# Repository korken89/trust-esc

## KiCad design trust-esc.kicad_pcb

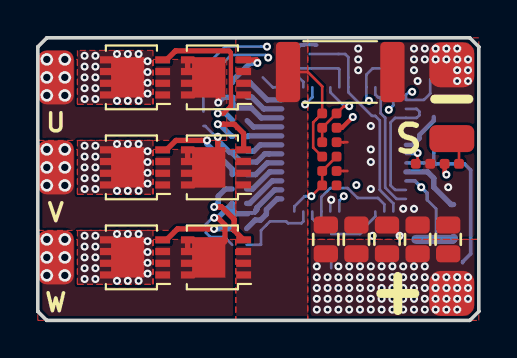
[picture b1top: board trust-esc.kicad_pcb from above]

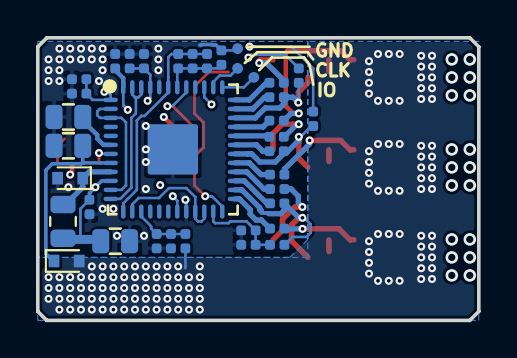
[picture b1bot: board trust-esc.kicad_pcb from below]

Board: 4 copper layers, 24.5 x 15.7 mm, 63 parts (37 on the bottom side), 41 nets.

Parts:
C101, C103, C106, C107, C108, C119: 0.1u; C_0402_1005Metric_Rounded
C102: 47u; C_0805
C104, C105, C111, C112, C113, C114, C116: 6.8u; C_0805
C117: 1n; C_0402_1005Metric_Rounded
C118: 100n; C_0402_1005Metric_Rounded
C501: 22p; C_0402_1005Metric_Rounded
C701, C801, C802: 47p; C_0402_1005Metric_Rounded
D101, D102: NSR05T30XV2T5G; D_SOD-523
J101, J102: Conn_01x01_Male; pad_2.5x2.5mm
J103: Conn_01x01_Male; pad_1.5x2.5mm
J104, J105, J106: Conn_01x01_Male; pad_circ_0.6mm
J201, J301, J401: Conn_01x01_Male; pad_3.0x2.0mm
L101: 22u; L_0805_2012Metric
Q201, Q202, Q301, Q302, Q401, Q402: BUK7M10-40EX; LFPAK33
R102: 100; R_0402_1005Metric_Rounded
R103: 1m; R_2512_6332Metric
R108, R110, R503, R504, R505, R506, R701, R801, R803: 47k; R_0402_1005Metric_Rounded
R109: 2.94k; R_0402_1005Metric_Rounded
R111, R702, R802, R804: 10k; R_0402_1005Metric_Rounded
R201, R202, R301, R302, R401, R402: 10; R_0402_1005Metric_Rounded
R501, R502: 1k; R_0402_1005Metric_Rounded
U101: STSPIN32F0; QFN-48-1EP_7x7mm_P0.5mm_EP2.8x2.8mm

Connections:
+3V3: C101.1, C102.1, C103.1, L101.1, R108.1, R504.2, U101.10, U101.48
+BATT: C111.2, C112.2, C113.2, C114.2, C116.2, D102.2, J101.1, Q201.5, Q301.5, Q401.5, R110.1
/HSU: R201.2, U101.33
/HSV: R301.2, U101.29
/HSW: R401.2, U101.25
/Half Bridge 1/GH: Q201.4, R201.1
/Half Bridge 1/GL: Q202.4, R202.1
/Half Bridge 2/GH: Q301.4, R301.1
/Half Bridge 2/GL: Q302.4, R302.1
/Half Bridge 3/GH: Q401.4, R401.1
/Half Bridge 3/GL: Q402.4, R402.1
/LSU: R202.2, U101.36
/LSV: R302.2, U101.32
/LSW: R402.2, U101.28
/NRST: C119.1, U101.7
/OC: C117.2, R108.2, R109.1, U101.24
/OP1O: U101.14, U101.21, U101.22
/OP1P: C802.1, R803.2, R804.1, U101.23
/OP2N: C501.1, R502.2, R505.1, R506.1, U101.42
/OP2O: C501.2, R505.2, R506.2, U101.13, U101.43
/OP2P: R501.1, R503.2, R504.1, U101.41
/OP3O: U101.12, U101.46, U101.47
/OP3P: C801.1, R801.2, R802.1, U101.45
/OP4O: U101.2, U101.3, U101.11
/OP4P: C701.1, R701.2, R702.1, U101.1
/PHASEU: C106.1, J201.1, Q201.1, Q201.2, Q201.3, Q202.5, R801.1, U101.34
/PHASEV: C107.1, J301.1, Q301.1, Q301.2, Q301.3, Q302.5, R701.1, U101.30
/PHASEW: C108.1, J401.1, Q401.1, Q401.2, Q401.3, Q402.5, R803.1, U101.26
/SWCLK: J105.1, U101.38
/SWIO: J104.1, U101.37
/UART_TX_RX: J103.1, R102.2
/VBAT_IN: C104.2, D102.1, U101.8
/VBAT_SENSE: C118.1, R110.2, R111.1, U101.15
/VR: Q202.1, Q202.2, Q202.3, Q302.1, Q302.2, Q302.3, Q402.1, Q402.2, Q402.3, R103.1, R109.2, R501.2
/VREG12: C105.2, U101.6
GND: C101.2, C102.2, C103.2, C104.1, C105.1, C111.1, C112.1, C113.1, C114.1, C116.1, C117.1, C118.2, C119.2, C701.2, C801.2, C802.2, D101.2, J102.1, J106.1, R103.2, R111.2, R502.1, R503.1, R702.2, R802.2, R804.2, U101.20, U101.44, U101.49
unnamed: C106.2, U101.35
unnamed: C107.2, U101.31
unnamed: C108.2, U101.27
unnamed: D101.1, L101.2, U101.9
unnamed: R102.1, U101.19, U101.39

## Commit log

2019-02-25 More additions and testing of PCB design
2019-02-26 Testing some more PCB ideas
2019-03-05 New output pads
2019-03-10 First routing complete
2019-03-11 New current sense resistor + silk fixes
